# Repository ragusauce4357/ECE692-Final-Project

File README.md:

# Logic Analyzer — Python GUI

This is the Python visualization frontend. It connects to the [Go signal decoder](https://github.com/ragusauce4357/ECE692-Final-Project/tree/feature/SignalDecoder) via TCP socket and renders 8-channel digital waveforms with UART, SPI, I2C, and CAN protocol decode overlays.

Just some initial work. We'll have stuff to work on for later.

## Setup

```bash
pip install -r requirements.txt
```

## Usage

```bash
# Test mode — simulated packets, no hardware needed
python gui.py --test

# Live mode — connects to Go decoder over TCP
python gui.py
```

## File Structure

| File | Description |
|------|-------------|
| `gui.py` | Entry point and main window |
| `decoder.py` | Constants, packet parsing, UART/SPI/I2C decoders |
| `transport.py` | TCP receiver, packet simulator, save/load |
| `display.py` | Waveform widget, CAN table, UI panels |
| `config.json` | User-editable runtime configuration |

## Configuration

We can edit the `config.json` file to set our default COM port, TCP host/port, baud rate, and which channels map to which protocol signals. Settings are loaded at startup and can also be changed from the UI.

## Packet Format

This ties back into the STM32 Firmware. The CAN bus has a header that's different than the logic headers (for UART, SPI, I2C) just for clarity. 
| Packet | Header | Seq | Payload | Checksum |
|--------|--------|-----|---------|----------|
| Logic  | `0xAA 0xBB` | 1B | 512 raw GPIO samples | XOR |
| CAN    | `0xCC 0xDD` | 1B | ID(2B) + DLC(1B) + data(0-8B) | XOR |

## Channel Map

This is pretty configurable, but here's a layout we can use. 

| Channel | Pin | Signal |
|---------|-----|--------|
| CH1 | PC1 | UART TX |
| CH2 | PC2 | UART RX |
| CH3 | PC3 | SPI CLK |
| CH4 | PC4 | SPI MOSI |
| CH5 | PC5 | SPI MISO |
| CH6 | PC6 | SPI CS |
| CH7 | PC7 | I2C SDA |
| CH8 | PC8 | I2C SCL |

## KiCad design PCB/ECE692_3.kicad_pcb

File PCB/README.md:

# PCB for Logic Analyzer

This will hold a PCB design for our logic analyzer. We're yet to decide whether we're going to do a complete PCB design, microcontroller and all, or just a 'shield' which connects to the morpho connectors. Regardless, those are the only two options... we will definitely need the USB 2.0 connection which the nucleo board itself doesn't directly provide. Below are our options. All prices are ballpark ofc.

## **Option 1:** Morpho Connector Shield

- If we take this option, we will only need to make a *shield* which goes on top of the existing STM32 microcontroller. This shield will have:
	- Male connectors, to connect to the morpho header pins on the STM32.
	- A 12 pin 90 degree male connector, hanging off the edge of the board. These will be the exposed 8 channels + 2 bxCAN + 2 grounds. The 8 channels will connect to pins PC1 to PC8 respectively, and CAN TX and RX to PB9 and PB8 respectively.
	- A USB connection, with DP on PA12, DM on PA11, VBUS connected to the 5V rail as well as PA9, and PA8 is also involved somehow, but idk how.
	- A level shifter, for the 8 channels (Bryan already got this)
- The budgeting will be:
	- Since this is a 2 layer board, the PCB alone will be either:
		- **$15** ($7 PCB, $8 shipping) if we opt for 24h fab time, but standard delivery (usually takes 10-14 days; need to order pronto)
		- **$30** ($7 PCB, $23 shipping) if we opt for 24h fab time, with DHL shipping 2-4 days. We will get the boards in a week or less after ordering if we do this.
	- Other parts from digikey/amazon:
		- **$5** Connectors. Although there's a high chance someone/somewhere on campus has this that we can permanently borrow :eyes:
		- **$2** USB connector. Chances are we'll definitely have to buy this from Digikey, unless someone on campus has some.
		- **$7** Digikey shipping. Applies unless we order off amazon.
	- So in total: **$30-45**. This will yield 5 completed boards, and is the lowest risk option, probably best for our case.
- Designing and ordering this pcb should be easy enough; we should be able to do it within a day.

## **Option 2:** Custom Board

- If we take this option, we'll have to do everything from the other option, plus the microcontroller itself, an LDO to convert the 5V from VBUS to 3v3 for the stm, crystal oscillators, status LEDs, etc. Stuff we'll need:
	- All the components from option 1
	- Capacitors, resistors, LEDs, crystals, and LDO.
	- 5x stm chips.
- The budgeting will be:
	- **$15 - $30** PCB costs are the same 
	- **$0** I have a few passive components and LDOs we can use 
	- **$16** Combined cost of components from option 1
	- **$40** 5x f446's from Digikey. We could also make just 2 or 3, which will lower the price.
	- In total for option 2: **$70-$85**. This will also yield 5 completed boards. There is higher risk, but it also grants us freedom to design it the way we want; form-factor, shape, etc.
- Designing and ordering this pcb will likely take 2-3 days.

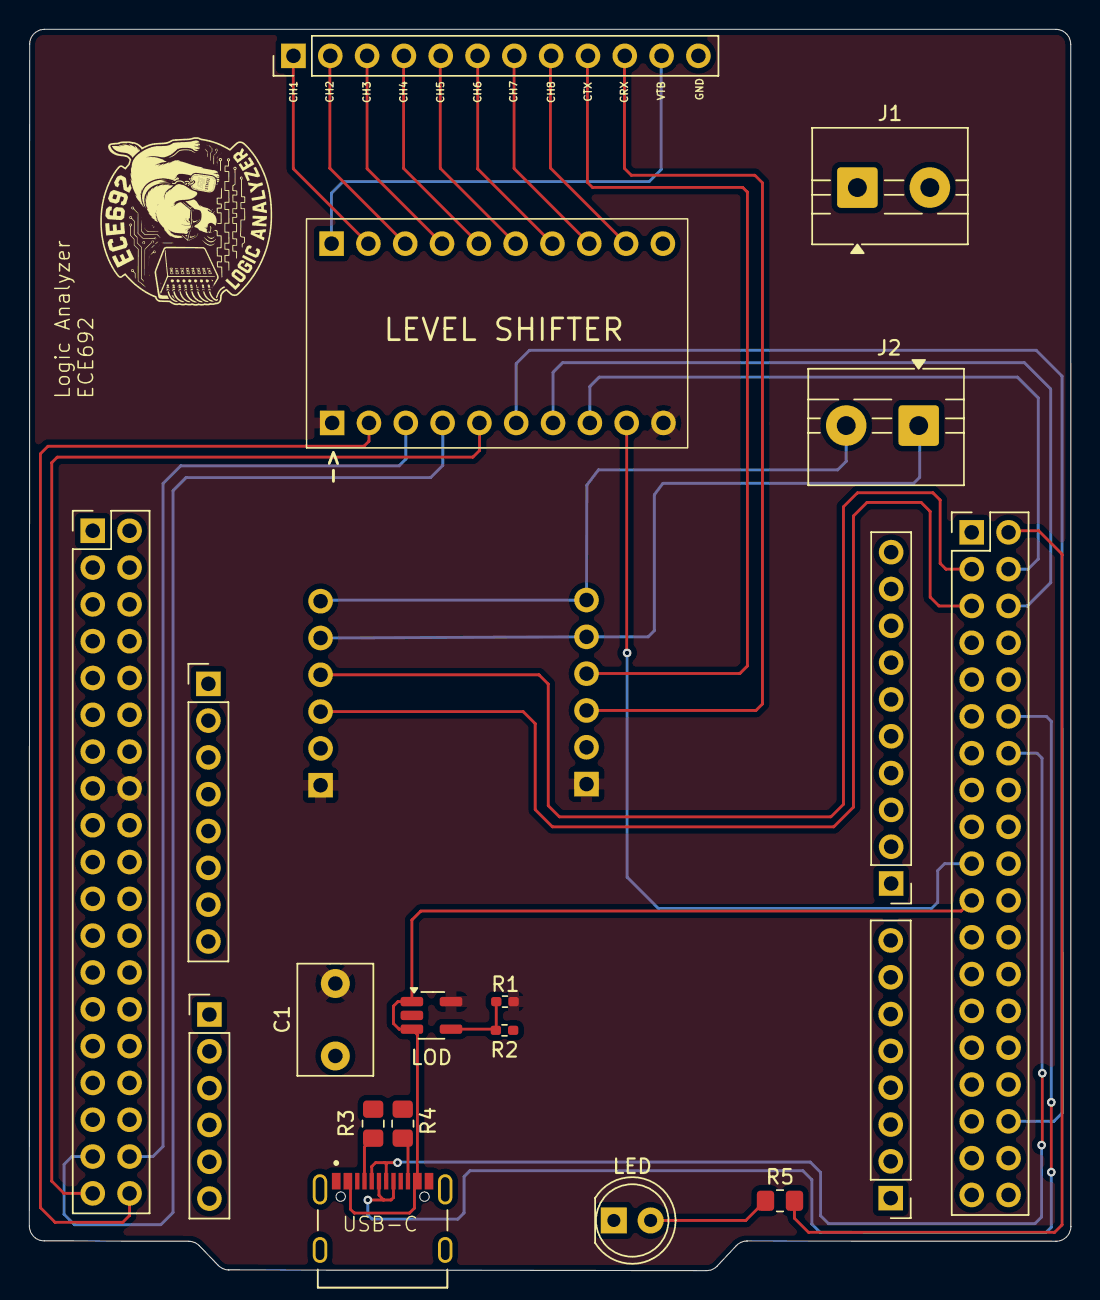
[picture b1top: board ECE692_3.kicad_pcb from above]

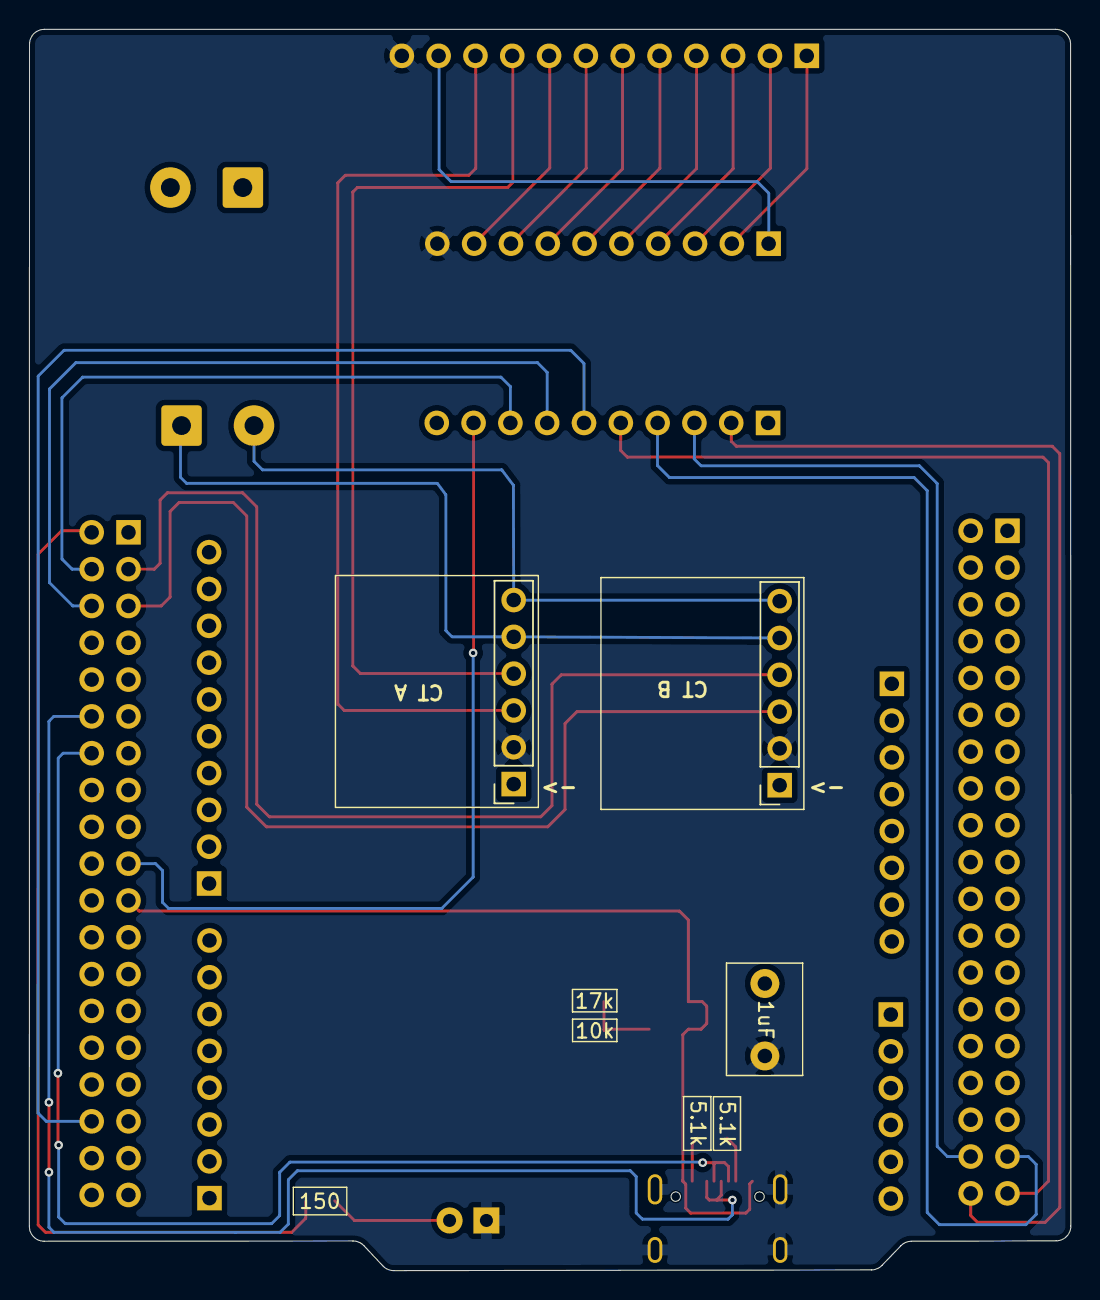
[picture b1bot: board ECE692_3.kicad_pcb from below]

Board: 2 copper layers, 71.9 x 85.6 mm, 17 parts (2 on the bottom side), 33 nets.

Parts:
C1: 1uF; C_Disc_D7.5mm_W5.0mm_P5.00mm
D1: LED; LED_D5.0mm
J1, J2: Screw_Terminal_01x02; TerminalBlock_MaiXu_MX126-5.0-02P_1x02_P5.00mm
J1#2: TYPE-C_16PIN_2MD__073_; SHOUHAN_TYPE-C_16PIN_2MD__073_
J2#2: Conn_01x12; PinHeader_1x12_P2.54mm_Vertical
R1: 17k; R_0402_1005Metric_Pad0.72x0.64mm_HandSolder
R2: 10k; R_0402_1005Metric_Pad0.72x0.64mm_HandSolder
R3, R4: 5.1k; R_0805_2012Metric_Pad1.20x1.40mm_HandSolder
R5: 150; R_0805_2012Metric_Pad1.20x1.40mm_HandSolder
U1: CAN_BUS_TRANSCEIVER1; PinSocket_1x06_P2.54mm_Vertical
U2: CAN_BUS_TRANSCEIVER2; PinSocket_1x06_P2.54mm_Vertical
U3: LOD; SOT-23-5_HandSoldering
U4: LEVEL_SHIFTER
U5, U6: NUCLEO-F446RE; PinHeader_2x19_P2.54mm_Vertical

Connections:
3V3: C1.1, R1.1, U1.1 (3V3), U2.1 (3V3), U3.5 (VOUT), U4.1 (VCCA), U4.10 (OE), U5.16 (CN7_+3V3)
CH1: U4.2 (A1), U5.38 (PC0/PB8)
CH2: U4.3 (A2), U5.36 (PC1/PB9)
CH3: U4.4 (A3), U5.35 (PC2)
CH4: U4.5 (A4), U5.37 (PC3)
CH5: U4.6 (A5), U6.34 (PC4)
CH6: U4.7 (A6), U6.6 (PC5)
CH7: U4.8 (A7), U6.4 (PC6)
CH8: U4.9 (A8), U6.19 (PC7)
CRX: U2.4 (CRX), U6.3 (PB8)
CRX_TB: J2#2.10, U1.3 (CTX)
CTX: U2.3 (CTX), U6.5 (PB9)
CTX_TB: J2#2.9, U1.4 (CRX)
D+: J1#2.A6 (DP1), J1#2.B6 (DP2), U6.12 (PA12)
D-: J1#2.A7 (DN1), J1#2.B7 (DN2), U6.14 (PA11)
GND: C1.2, D1.1 (K), J1#2.A1_B12 (GND_A), J1#2.B1_A12 (GND_B), J1#2.SH1 (SHIELD), J1#2.SH2 (SHIELD), J1#2.SH3 (SHIELD), J1#2.SH4 (SHIELD), J2#2.12, R2.2, R3.1, R4.2, U1.2 (GND), U2.2 (GND), U3.2 (GND), U4.20 (GND)
unnamed: D1.2 (A), R5.1
unnamed: J1#2.A5 (CC1), R3.2
unnamed: J1#2.B5 (CC2), R4.1
unnamed: J1.1, J2.1, U1.5 (CANH), U2.5 (CANH)
unnamed: J1.2, J2.2, U1.6 (CANL), U2.6 (CANL)
unnamed: R1.2, R2.1, U3.4 (ADJ)
unnamed: R5.2, U6.2 (PC8)
TB_CH1: J2#2.1, U4.12 (B1)
TB_CH2: J2#2.2, U4.13 (B2)
TB_CH3: J2#2.3, U4.14 (B3)
TB_CH4: J2#2.4, U4.15 (B4)
TB_CH5: J2#2.5, U4.16 (B5)
TB_CH6: J2#2.6, U4.17 (B6)
TB_CH7: J2#2.7, U4.18 (B7)
TB_CH8: J2#2.8, U4.19 (B8)
VBUS: J1#2.A4_B9 (VBUS_A), J1#2.B4_A9 (VBUS_B), U3.1 (5V), U3.3 (EN), U6.21 (PA9)
V_TB: J2#2.11, U4.11 (VCCB)

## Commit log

2026-03-17 added markdown to HTML converter script, modified gitignore accordingly
2026-03-17 added documentation PDFs for the stm32
2026-03-17 added ideas spreadsheet link in README
2026-04-09 updated the readme
2026-04-10 removed PCA9309 from list
2026-04-13 added initial Software.ioc file from CubeMX
2026-04-13 added changelog for firmware
2026-04-14 Finished the CubeMX configuration.
2026-04-15 updated gitignore
2026-04-15 Changes to the STM32 receiver CubeMX config
2026-04-15 Added a Draw.io file, hopefully it helps to visualize the setup a little better
2026-04-16 added a Doxyfile
2026-04-19 updated the changelog
2026-04-20 fixed a USB CDC declaration error
2026-04-20 Initial GUI implementation. Basic stuff, haven't even finished the decoder yet, so still need to work on it
2026-04-20 updated CHANGELOG
2026-04-21 added initial Kicad project
2026-04-25 Update CHANGELOG with GUI enhancements
    Updated CHANGELOG with new features and changes for the GUI, including a blue checkmark for checkboxes, improved resizing behavior, and tabbed panels.
2026-04-25 Removed the .metadata from tracking, added .gitignore. We need a folder for Software/Transmitter thats why.
2026-04-25 Changed Software/ to firmware-receiver/. Added a firmware-transmitter/ folder so we can work on it. Just did initial pin and clock configurations.
2026-04-25 updated gitignore. misspelled metadata last time :(
2026-04-25 fixed gitignores, file structure should be good
2026-04-26 added cli argument to list available ports
2026-04-26 Moved status LED to PC8 and shifted the channels down to PC0-PC7. Reverted the code back to DMA byte data width and changed accordingly.
2026-04-26 Added Debug, Release, and .metadata to .gitignore
2026-04-27 Added initial code for serial package. IT DOESN'T WORK YET!
    - Added a function that runs as a goroutine and forwards data to channel
    - Also added a temporary verification function, but some reason it
    doesn't print??? Not sure why
2026-04-27 added a changelog
2026-04-27 Update serial parser, config, and test scripts to match packet protocol
2026-04-28 Finished the PCB
    - Finished the PCB and ordered at JLCPCB
    - Uploaded schematic pdf, and image of complete layout and routing
2026-04-29 Added the initial UART decoder. Haven't tested fully if it works yet
2026-05-01 deleted pycache in gui
2026-05-01 removed capture test binary file.
2026-05-01 updated the changelog to be upto date with commit 10a24d3
2026-05-02 added 'baud' cli argument to specify transmitter baud
2026-05-02 use this for testing WITHOUT the usb
